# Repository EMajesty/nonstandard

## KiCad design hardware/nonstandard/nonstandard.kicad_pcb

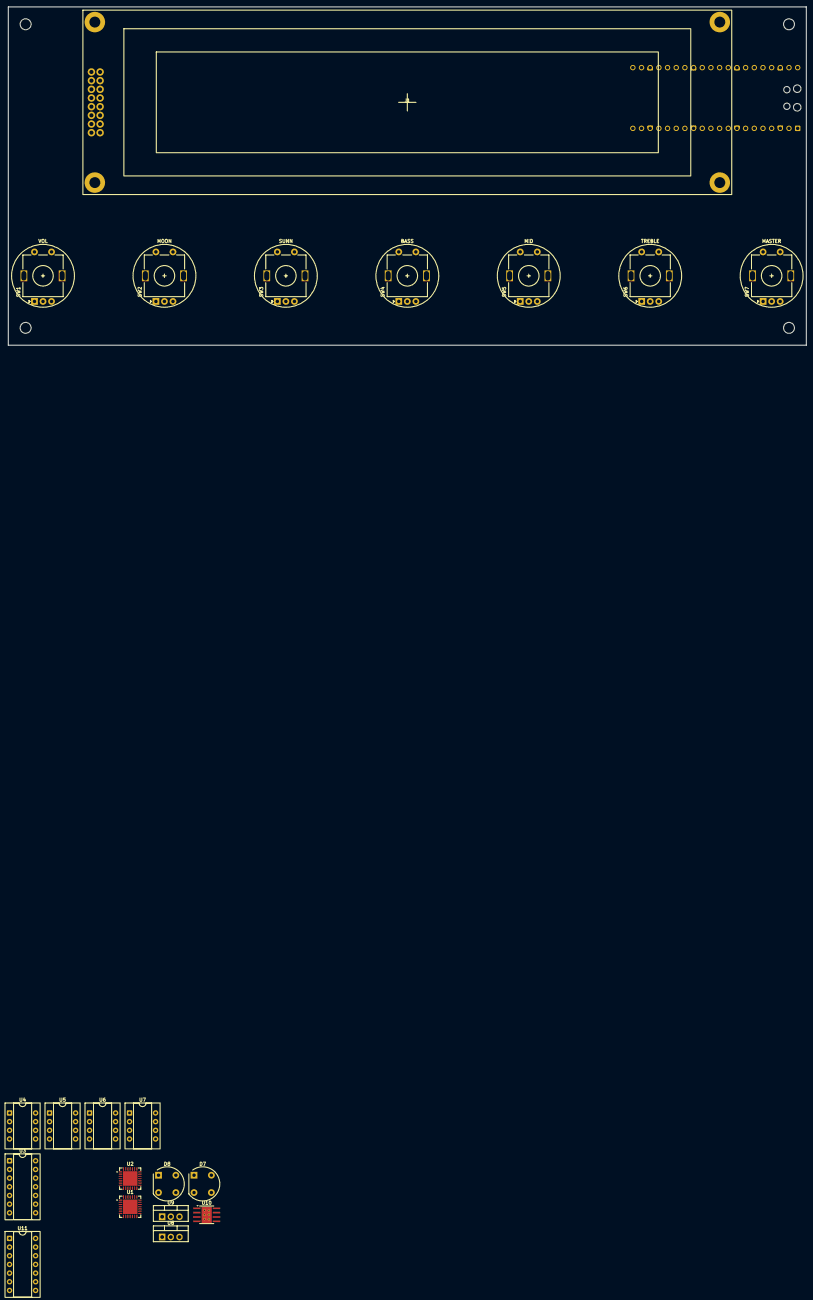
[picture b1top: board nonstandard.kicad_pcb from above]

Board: 2 copper layers, 233.7 x 99.1 mm, 22 parts (1 on the bottom side), 41 nets, no tracks yet.

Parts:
A1: RaspberryPi_Pico; RaspberryPi_Pico_Common_Unspecified
D7, D8: W01G; Diode_Bridge_Round_D9.8mm
J1: LCD; 4004
SW1: VOL; RotaryEncoder_Alps_EC11E-Switch_Vertical_H20mm
SW2: MOON; RotaryEncoder_Alps_EC11E-Switch_Vertical_H20mm
SW3: SUNN; RotaryEncoder_Alps_EC11E-Switch_Vertical_H20mm
SW4: BASS; RotaryEncoder_Alps_EC11E-Switch_Vertical_H20mm
SW5: MID; RotaryEncoder_Alps_EC11E-Switch_Vertical_H20mm
SW6: TREBLE; RotaryEncoder_Alps_EC11E-Switch_Vertical_H20mm
SW7: MASTER; RotaryEncoder_Alps_EC11E-Switch_Vertical_H20mm
U1, U2: MCP23S17_ML; QFN-28-1EP_6x6mm_P0.65mm_EP4.25x4.25mm
U3, U11: 4069UB; CERDIP-14_W7.62mm_SideBrazed_Socket
U4, U5, U6, U7: Opamp_Dual; CERDIP-8_W7.62mm_SideBrazed_Socket
U8: LM7824_TO220; TO-220-3_Vertical
U9: LM7808_TO220; TO-220-3_Vertical
U10: LMR36510ADDA; Texas_HTSOP-8-1EP_3.9x4.9mm_P1.27mm_EP2.95x4.9mm_Mask2.4x3.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

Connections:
+3.3V: A1.36 (3V3), U1.5 (VDD), U2.5 (VDD), U2.11 (A0)
+5V: A1.39 (VSYS), J1.14
+8V: U9.3 (VO), U11.7 (VSS)
+24V: U8.3 (VO), U9.1 (VI)
E1A: SW1.A, U1.17 (GPA0)
E1B: SW1.B, U1.18 (GPA1)
E2A: SW2.A, U1.19 (GPA2)
E2B: SW2.B, U1.20 (GPA3)
E3A: SW3.A, U1.21 (GPA4)
E3B: SW3.B, U1.22 (GPA5)
E4A: SW4.A, U1.23 (GPA6)
E4B: SW4.B, U1.24 (GPA7)
E5A: SW5.A, U1.25 (GPB0)
E5B: SW5.B, U1.26 (GPB1)
E6A: SW6.A, U1.27 (GPB2)
E6B: SW6.B, U1.28 (GPB3)
E7A: SW7.A, U1.1 (GPB4)
E7B: SW7.B, U1.2 (GPB5)
GND: A1.3 (GND), A1.8 (GND), A1.13 (GND), A1.18 (GND), A1.23 (GND), A1.28 (GND), A1.33 (AGND), A1.38 (GND), D7.3 (-), J1.10, J1.13, SW1.C, SW1.MP, SW1.S2, SW2.C, SW2.MP, SW2.S2, SW3.C, SW3.MP, SW3.S2, SW4.C, SW4.MP, SW4.S2, SW5.C, SW5.MP, SW5.S2, SW6.C, SW6.MP, SW6.S2, SW7.C, SW7.MP, SW7.S2, U1.6 (VSS), U1.11 (A0), U1.12 (A1), U1.13 (A2), U1.29 (EP), U2.6 (VSS), U2.12 (A1), U2.13 (A2), U2.29 (EP), U4.3 (+), U4.5 (+), U5.3 (+), U7.3 (+), U8.2 (GND), U9.2 (GND), U10.1 (PGND), U10.9 (PAD), U11.11, U11.13, U11.14 (VDD)
LCD_DB0: A1.14 (GPIO10), J1.8
LCD_DB1: A1.15 (GPIO11), J1.7
LCD_DB2: A1.16 (GPIO12), J1.6
LCD_DB3: A1.17 (GPIO13), J1.5
LCD_E1: A1.10 (GPIO7), J1.9
LCD_E2: A1.11 (GPIO8), J1.15
LCD_RS: A1.12 (GPIO9), J1.11
MCP_CS: A1.7 (GPIO5), U1.7 (~CS), U2.7 (~CS)
MCP_INT: A1.9 (GPIO6), U1.16 (INTA), U2.16 (INTA)
MCP_SCK: A1.4 (GPIO2), U1.8 (SCK), U2.8 (SCK)
MCP_SI: A1.6 (GPIO4), U1.9 (SI), U2.9 (SI)
MCP_SO: A1.5 (GPIO3), U1.10 (SO), U2.10 (SO)
unnamed: U5.6 (-), U5.7
unnamed: U6.1, U6.2 (-)
SW1: SW1.S1, U2.17 (GPA0)
SW2: SW2.S1, U2.18 (GPA1)
SW3: SW3.S1, U2.19 (GPA2)
SW4: SW4.S1, U2.20 (GPA3)
SW5: SW5.S1, U2.21 (GPA4)
SW6: SW6.S1, U2.22 (GPA5)
SW7: SW7.S1, U2.23 (GPA6)
VAUX_RAW: D7.1 (+), U8.1 (VI), U10.2 (VIN), U10.3 (EN)
